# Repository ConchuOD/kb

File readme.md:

# Custom keyboard

Things that are sub-optimal:
- mounting holes are M2 when M3 would be better.
- SOD323 are needlessly small, requiring better soldering gear than is reasonable.

Thanks to Jorge Reyes for his simple T3.2 model: https://grabcad.com/library/teensy-3-1-3-2-1
Thanks also to Constantin for his eagle teensy models that I converted to use in kicad https://forum.pjrc.com/threads/24637-Updated-Teensy-3-1-and-Teensy-3-0-Eagle-libraries

After 2 years, I finally got myself a 3d printer. I might finally finish this :)

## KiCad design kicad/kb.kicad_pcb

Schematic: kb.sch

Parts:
A1: CHERRY-MX; SW_Cherry_MX_1.00u_PCB
B1: CHERRY-MX; SW_Cherry_MX_1.00u_PCB
BCKT1: CHERRY-MX; SW_Cherry_MX_1.00u_PCB
BKSP1: CHERRY-MX; SW_Cherry_MX_2.00u_PCB
BSLH1: CHERRY-MX; SW_Cherry_MX_1.00u_PCB
C1: CHERRY-MX; SW_Cherry_MX_1.00u_PCB
CAPS1: CHERRY-MX; SW_Cherry_MX_1.75u_PCB
COLON1: CHERRY-MX; SW_Cherry_MX_1.00u_PCB
COMMA1: CHERRY-MX; SW_Cherry_MX_1.00u_PCB
D1, D2, D3, D4, D5, D6, D7, D8, D9, D10, D11, D12, D13, D14, D15, D16, D17, D18, D19, D20, D21, D22, D23, D24, D25, D26, D27, D28, D29, D30, D31, D32, D33, D34, D35, D36, D37, D38, D39, D40, D41, D42, D43, D44, D45, D46, D47, D48, D49, D50, D51, D52, D53, D54, D55, D56, D57, D58, D59, D60, D61, D62, D63, D64, D65, D66, D67, D68, D69, D70, D71, D72, D73, D74, D75, D76, D77, D78, D79, D80, D81, D82, D84, D85, D86, D87, D88, D89, D90, D91, D92, D93, D94: 1N4148WS; DIODES_SOD-323
D83: CHERRY-MX; SW_Cherry_MX_1.00u_PCB
E1: CHERRY-MX; SW_Cherry_MX_1.00u_PCB
EIGHT1: CHERRY-MX; SW_Cherry_MX_1.00u_PCB
ENTER1: CHERRY-MX; SW_Cherry_MX_ISOEnter_PCB
EQL1: CHERRY-MX; SW_Cherry_MX_1.00u_PCB
ESC1: CHERRY-MX; SW_Cherry_MX_1.00u_PCB
F1, F2, F3, F4, F5, F6, F7, F8, F9, F10, F11, F12, F13: CHERRY-MX; SW_Cherry_MX_1.00u_PCB
FIVE1: CHERRY-MX; SW_Cherry_MX_1.00u_PCB
FN1: CHERRY-MX; SW_Cherry_MX_1.25u_PCB
FOUR1: CHERRY-MX; SW_Cherry_MX_1.00u_PCB
FSH1: CHERRY-MX; SW_Cherry_MX_1.00u_PCB
FSTOP1: CHERRY-MX; SW_Cherry_MX_1.00u_PCB
G1: CHERRY-MX; SW_Cherry_MX_1.00u_PCB
H1: CHERRY-MX; SW_Cherry_MX_1.00u_PCB
HASH1: CHERRY-MX; SW_Cherry_MX_1.00u_PCB
I1: CHERRY-MX; SW_Cherry_MX_1.00u_PCB
J1: CHERRY-MX; SW_Cherry_MX_1.00u_PCB
K1: CHERRY-MX; SW_Cherry_MX_1.00u_PCB
L1: CHERRY-MX; SW_Cherry_MX_1.00u_PCB
LALT1: CHERRY-MX; SW_Cherry_MX_1.25u_PCB
LCTRL1: CHERRY-MX; SW_Cherry_MX_1.25u_PCB
LOS1: CHERRY-MX; SW_Cherry_MX_1.25u_PCB
LSB1: CHERRY-MX; SW_Cherry_MX_1.00u_PCB
LSHFT1: CHERRY-MX; SW_Cherry_MX_1.25u_PCB
M1: CHERRY-MX; SW_Cherry_MX_1.00u_PCB
MINUS1: CHERRY-MX; SW_Cherry_MX_1.00u_PCB
N1, N2, N3, N4, N5, N6, N7, N8, N9, N10: CHERRY-MX; SW_Cherry_MX_1.00u_PCB
NDOT1: CHERRY-MX; SW_Cherry_MX_1.00u_PCB
NINE1: CHERRY-MX; SW_Cherry_MX_1.00u_PCB
NINUS1: CHERRY-MX; SW_Cherry_MX_1.00u_PCB
NNTER1: CHERRY-MX; SW_Cherry_MX_2.00u_Vertical_PCB
NPLUS1: CHERRY-MX; SW_Cherry_MX_2.00u_Vertical_PCB
NSLSH1: CHERRY-MX; SW_Cherry_MX_1.00u_PCB
NSTAR1: CHERRY-MX; SW_Cherry_MX_1.00u_PCB
NUMLK1: CHERRY-MX; SW_Cherry_MX_1.00u_PCB
NZERO1: CHERRY-MX; SW_Cherry_MX_1.00u_PCB
NZZERO1: CHERRY-MX; SW_Cherry_MX_1.00u_PCB
O1: CHERRY-MX; SW_Cherry_MX_1.00u_PCB
ONE1: CHERRY-MX; SW_Cherry_MX_1.00u_PCB
P1: CHERRY-MX; SW_Cherry_MX_1.00u_PCB
Q1: CHERRY-MX; SW_Cherry_MX_1.00u_PCB
R1: CHERRY-MX; SW_Cherry_MX_1.00u_PCB
RALT1: CHERRY-MX; SW_Cherry_MX_1.25u_PCB
RCTRL1: CHERRY-MX; SW_Cherry_MX_1.25u_PCB
ROS1: CHERRY-MX; SW_Cherry_MX_1.25u_PCB
RSB1: CHERRY-MX; SW_Cherry_MX_1.00u_PCB
RSHFT1: CHERRY-MX; SW_Cherry_MX_2.75u_PCB
S1: CHERRY-MX; SW_Cherry_MX_1.00u_PCB
SEVEN1: CHERRY-MX; SW_Cherry_MX_1.00u_PCB
SIX1: CHERRY-MX; SW_Cherry_MX_1.00u_PCB
SPACE1: CHERRY-MX; SW_Cherry_MX_6.25u_PCB
T1: CHERRY-MX; SW_Cherry_MX_1.00u_PCB
T32: TEENSY_3.1-3.2_DIL; TEENSY_3.0-3.2&LC_DIL
TAB1: CHERRY-MX; SW_Cherry_MX_1.50u_PCB
THREE1: CHERRY-MX; SW_Cherry_MX_1.00u_PCB
TICK1: CHERRY-MX; SW_Cherry_MX_1.00u_PCB
TP13: TestPoint; TestPoint_Pad_D1.0mm
TPCOL0, TPCOL1, TPCOL2, TPCOL3, TPCOL4, TPCOL5, TPCOL6, TPCOL7, TPCOL8, TPCOL9, TPCOL10, TPCOL11, TPCOL12: TestPoint; TestPoint_Pad_D1.0mm
TPROW0, TPROW1, TPROW2, TPROW3, TPROW4, TPROW5, TPROW6: TestPoint; TestPoint_Pad_D1.0mm
TWO1: CHERRY-MX; SW_Cherry_MX_1.00u_PCB
U1: CHERRY-MX; SW_Cherry_MX_1.00u_PCB
V1: CHERRY-MX; SW_Cherry_MX_1.00u_PCB
W1: CHERRY-MX; SW_Cherry_MX_1.00u_PCB
X1: CHERRY-MX; SW_Cherry_MX_1.00u_PCB
Y1: CHERRY-MX; SW_Cherry_MX_1.00u_PCB
Z1: CHERRY-MX; SW_Cherry_MX_1.00u_PCB
ZERO1: CHERRY-MX; SW_Cherry_MX_1.00u_PCB

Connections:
+3V3: T32.3.3V
+5V: T32.VIN
/COL0: D1.C, D2.C, D3.C, D4.C, D5.C, D6.C, D8.C, T32.0, TPCOL0.1
/COL1: D7.C, D9.C, D10.C, D11.C, D12.C, D13.C, D14.C, T32.1, TPCOL1.1
/COL2: D15.C, D16.C, D17.C, D18.C, D19.C, D20.C, D22.C, T32.2, TPCOL2.1
/COL3: D21.C, D24.C, D25.C, D26.C, D27.C, D28.C, D62.C, T32.3, TPCOL3.1
/COL4: D29.C, D30.C, D31.C, D32.C, D33.C, D34.C, D61.C, T32.4, TPCOL4.1
/COL5: D23.C, D35.C, D60.C, D64.C, D65.C, D66.C, D67.C, T32.5, TPCOL5.1
/COL6: D36.C, D37.C, D38.C, D39.C, D40.C, D63.C, T32.6, TPCOL6.1
/COL7: D42.C, D43.C, D44.C, D45.C, D46.C, T32.7, TPCOL7.1
/COL8: D48.C, D49.C, D50.C, D51.C, D52.C, D53.C, T32.8, TPCOL8.1
/COL9: D54.C, D55.C, D56.C, D57.C, D58.C, D59.C, D74.C, T32.9, TPCOL9.1
/COL10: D69.C, D70.C, D71.C, D72.C, D77.C, D79.C, D80.C, T32.10, TPCOL10.1
/COL11: D41.C, D47.C, D75.C, D76.C, D84.C, D85.C, D86.C, T32.11, TPCOL11.1
/COL12: D87.C, D88.C, D89.C, D90.C, D91.C, D92.C, T32.12, TPCOL12.1
/COL13: D68.C, D73.C, D78.C, D81.C, D82.C, D93.C, D94.C, T32.13, TP13.1
/N$1: D1.A, ESC1.SW2 (PIN-2)
/N$2: BCKT1.SW2 (PIN-2), D2.A
/N$3: D3.A, TAB1.SW2 (PIN-2)
/N$4: CAPS1.SW2 (PIN-2), D4.A
/N$5: D5.A, LSHFT1.SW2 (PIN-2)
/N$6: D6.A, LCTRL1.SW2 (PIN-2)
/N$7: D8.A, ONE1.SW2 (PIN-2)
/N$8: D9.A, Q1.SW2 (PIN-2)
/N$9: A1.SW2 (PIN-2), D10.A
/N$10: BSLH1.SW2 (PIN-2), D11.A
/N$11: D12.A, LOS1.SW2 (PIN-2)
/N$12: D13.A, TWO1.SW2 (PIN-2)
/N$13: D14.A, W1.SW2 (PIN-2)
/N$14: D15.A, S1.SW2 (PIN-2)
/N$15: D16.A, Z1.SW2 (PIN-2)
/N$16: D17.A, LALT1.SW2 (PIN-2)
/N$17: D7.A, F1.SW2 (PIN-2)
/N$18: D19.A, THREE1.SW2 (PIN-2)
/N$19: D20.A, E1.SW2 (PIN-2)
/N$20: D21.A, D83.SW2 (PIN-2)
/N$21: D22.A, X1.SW2 (PIN-2)
/N$22: D29.A, SIX1.SW2 (PIN-2)
/N$23: D18.A, F2.SW2 (PIN-2)
/N$24: D25.A, FOUR1.SW2 (PIN-2)
/N$25: D26.A, R1.SW2 (PIN-2)
/N$26: D27.A, F13.SW2 (PIN-2)
/N$27: C1.SW2 (PIN-2), D28.A
/N$28: D35.A, Y1.SW2 (PIN-2)
/N$29: D24.A, F3.SW2 (PIN-2)
/N$30: D31.A, FIVE1.SW2 (PIN-2)
/N$31: D32.A, T1.SW2 (PIN-2)
/N$32: D33.A, G1.SW2 (PIN-2)
/N$33: D34.A, V1.SW2 (PIN-2)
/N$34: D60.A, H1.SW2 (PIN-2)
/N$35: D30.A, F4.SW2 (PIN-2)
/N$36: D37.A, EIGHT1.SW2 (PIN-2)
/N$37: D38.A, I1.SW2 (PIN-2)
/N$38: D39.A, K1.SW2 (PIN-2)
/N$39: D40.A, M1.SW2 (PIN-2)
/N$40: D41.A, NUMLK1.SW2 (PIN-2)
/N$41: D36.A, F7.SW2 (PIN-2)
/N$42: D43.A, NINE1.SW2 (PIN-2)
/N$43: D44.A, O1.SW2 (PIN-2)
/N$44: D45.A, L1.SW2 (PIN-2)
/N$45: COMMA1.SW2 (PIN-2), D46.A
/N$46: D47.A, NZERO1.SW2 (PIN-2)
/N$47: D42.A, F8.SW2 (PIN-2)
/N$48: D49.A, ZERO1.SW2 (PIN-2)
/N$49: D50.A, P1.SW2 (PIN-2)
/N$50: COLON1.SW2 (PIN-2), D51.A
/N$51: D52.A, FSTOP1.SW2 (PIN-2)
/N$52: D53.A, RALT1.SW2 (PIN-2)
/N$53: D48.A, F9.SW2 (PIN-2)
/N$54: D55.A, MINUS1.SW2 (PIN-2)
/N$55: D56.A, LSB1.SW2 (PIN-2)
/N$56: D57.A, TICK1.SW2 (PIN-2)
/N$57: D58.A, FSH1.SW2 (PIN-2)
/N$58: D59.A, ROS1.SW2 (PIN-2)
/N$59: D54.A, F10.SW2 (PIN-2)
/N$60: B1.SW2 (PIN-2), D61.A
/N$61: D62.A, SPACE1.SW2 (PIN-2)
/N$62: D23.A, F5.SW2 (PIN-2)
/N$63: D64.A, SEVEN1.SW2 (PIN-2)
/N$64: D65.A, U1.SW2 (PIN-2)
/N$65: D66.A, J1.SW2 (PIN-2)
/N$66: D67.A, N10.SW2 (PIN-2)
/N$67: D68.A, NDOT1.SW2 (PIN-2)
/N$68: D63.A, F6.SW2 (PIN-2)
/N$69: D70.A, EQL1.SW2 (PIN-2)
/N$70: D71.A, RSB1.SW2 (PIN-2)
/N$71: D72.A, HASH1.SW2 (PIN-2)
/N$72: D78.A, NPLUS1.SW2 (PIN-2)
/N$73: D74.A, FN1.SW2 (PIN-2)
/N$74: D69.A, F11.SW2 (PIN-2)
/N$75: BKSP1.SW2 (PIN-2), D76.A
/N$76: D77.A, ENTER1.SW2 (PIN-2)
/N$77: D81.A, N9.SW2 (PIN-2)
/N$78: D79.A, RSHFT1.SW2 (PIN-2)
/N$79: D80.A, RCTRL1.SW2 (PIN-2)
/N$80: D75.A, F12.SW2 (PIN-2)
/N$81: D82.A, N6.SW2 (PIN-2)
/N$83: D84.A, N7.SW2 (PIN-2)
/N$84: D85.A, N4.SW2 (PIN-2)
/N$85: D86.A, N1.SW2 (PIN-2)
/N$86: D93.A, N3.SW2 (PIN-2)
/N$87: D88.A, NSLSH1.SW2 (PIN-2)
/N$88: D89.A, N8.SW2 (PIN-2)
/N$89: D90.A, N5.SW2 (PIN-2)
/N$90: D91.A, N2.SW2 (PIN-2)
/N$91: D92.A, NZZERO1.SW2 (PIN-2)
/N$92: D87.A, NSTAR1.SW2 (PIN-2)
/N$93: D94.A, NNTER1.SW2 (PIN-2)
/N$94: D73.A, NINUS1.SW2 (PIN-2)
/ROW0: ESC1.SW1 (PIN-1), F1.SW1 (PIN-1), F2.SW1 (PIN-1), F3.SW1 (PIN-1), F4.SW1 (PIN-1), F5.SW1 (PIN-1), F6.SW1 (PIN-1), F8.SW1 (PIN-1), F9.SW1 (PIN-1), F10.SW1 (PIN-1), F11.SW1 (PIN-1), F12.SW1 (PIN-1), NINUS1.SW1 (PIN-1), NSTAR1.SW1 (PIN-1), T32.17/A3, TPROW0.1
/ROW1: BKSP1.SW1 (PIN-1), EQL1.SW1 (PIN-1), F7.SW1 (PIN-1), FIVE1.SW1 (PIN-1), FOUR1.SW1 (PIN-1), MINUS1.SW1 (PIN-1), NINE1.SW1 (PIN-1), NPLUS1.SW1 (PIN-1), NSLSH1.SW1 (PIN-1), ONE1.SW1 (PIN-1), SEVEN1.SW1 (PIN-1), T32.18/A4, THREE1.SW1 (PIN-1), TPROW1.1, TWO1.SW1 (PIN-1), ZERO1.SW1 (PIN-1)
/ROW2: BCKT1.SW1 (PIN-1), E1.SW1 (PIN-1), EIGHT1.SW1 (PIN-1), LSB1.SW1 (PIN-1), N8.SW1 (PIN-1), N9.SW1 (PIN-1), NUMLK1.SW1 (PIN-1), O1.SW1 (PIN-1), P1.SW1 (PIN-1), R1.SW1 (PIN-1), RSB1.SW1 (PIN-1), SIX1.SW1 (PIN-1), T32.19/A5, TPROW2.1, W1.SW1 (PIN-1), Y1.SW1 (PIN-1)
/ROW3: COLON1.SW1 (PIN-1), D83.SW1 (PIN-1), ENTER1.SW1 (PIN-1), I1.SW1 (PIN-1), L1.SW1 (PIN-1), N5.SW1 (PIN-1), N6.SW1 (PIN-1), N7.SW1 (PIN-1), Q1.SW1 (PIN-1), S1.SW1 (PIN-1), T1.SW1 (PIN-1), T32.20/A6, TAB1.SW1 (PIN-1), TICK1.SW1 (PIN-1), TPROW3.1, U1.SW1 (PIN-1)
/ROW4: A1.SW1 (PIN-1), CAPS1.SW1 (PIN-1), COMMA1.SW1 (PIN-1), F13.SW1 (PIN-1), FSH1.SW1 (PIN-1), FSTOP1.SW1 (PIN-1), G1.SW1 (PIN-1), H1.SW1 (PIN-1), HASH1.SW1 (PIN-1), K1.SW1 (PIN-1), N2.SW1 (PIN-1), N3.SW1 (PIN-1), N4.SW1 (PIN-1), T32.21/A7, TPROW4.1, Z1.SW1 (PIN-1)
/ROW5: BSLH1.SW1 (PIN-1), C1.SW1 (PIN-1), J1.SW1 (PIN-1), LSHFT1.SW1 (PIN-1), M1.SW1 (PIN-1), N1.SW1 (PIN-1), NNTER1.SW1 (PIN-1), NZZERO1.SW1 (PIN-1), RALT1.SW1 (PIN-1), ROS1.SW1 (PIN-1), RSHFT1.SW1 (PIN-1), T32.22/A8, TPROW5.1, V1.SW1 (PIN-1), X1.SW1 (PIN-1)
/ROW6: B1.SW1 (PIN-1), FN1.SW1 (PIN-1), LALT1.SW1 (PIN-1), LCTRL1.SW1 (PIN-1), LOS1.SW1 (PIN-1), N10.SW1 (PIN-1), NDOT1.SW1 (PIN-1), NZERO1.SW1 (PIN-1), RCTRL1.SW1 (PIN-1), SPACE1.SW1 (PIN-1), T32.23/A9, TPROW6.1
GND: T32.AGND, T32.GND

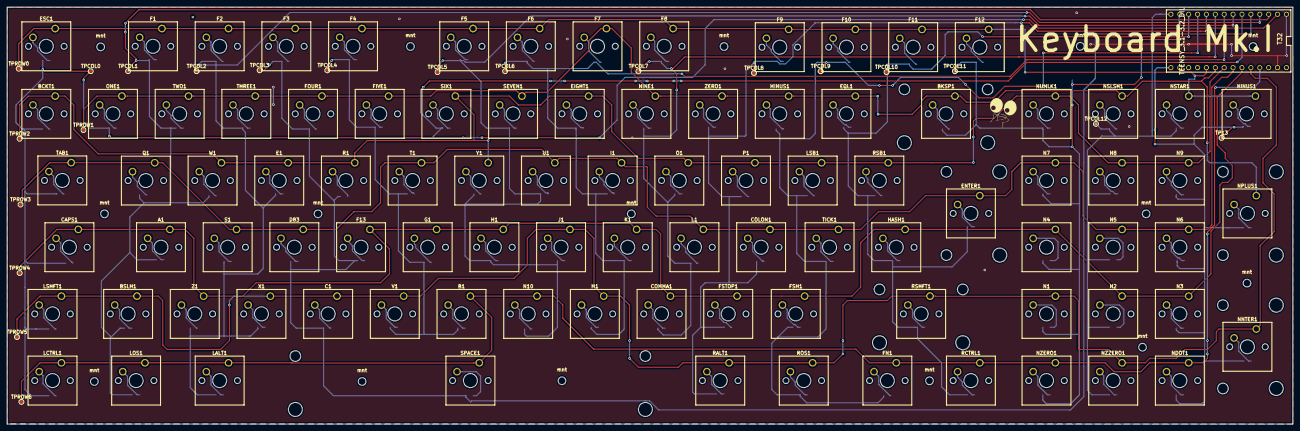
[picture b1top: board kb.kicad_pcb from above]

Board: 2 copper layers, 367.3 x 119.1 mm, 223 parts (0 on the bottom side), 115 nets.

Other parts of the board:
mnt: MountingHole_2.2mm_M2
mnt#2, mnt#3, mnt#4, mnt#5, mnt#6, mnt#7, mnt#8, mnt#9, mnt#10, mnt#11, mnt#12, mnt#13, mnt#14, mnt#15: MountingHole_2.2mm_M2

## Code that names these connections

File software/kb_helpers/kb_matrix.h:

#ifndef KB_MATRIX_H_
#define KB_MATRIX_H_

#include <kinetis.h>
#include <Arduino.h>
#include "keycodes.h"

#define COL0_PIN  0
#define COL1_PIN  1
#define COL2_PIN  2
#define COL3_PIN  3
#define COL4_PIN  4
#define COL5_PIN  5
#define COL6_PIN  6
#define COL7_PIN  7
#define COL8_PIN  8
#define COL9_PIN  9
#define COL10_PIN 10
#define COL11_PIN 11
#define COL12_PIN 12
#define COL13_PIN 13

#define ROW0_PIN  17
#define ROW1_PIN  18
#define ROW2_PIN  19
#define ROW3_PIN  20
#define ROW4_PIN  21
#define ROW5_PIN  22
#define ROW6_PIN  23

#define NUM_ROWS  7
#define NUM_COLS  14

static const uint16_t matrix_to_keycode[NUM_ROWS * NUM_COLS] = {
    KC_ESC,   KC_ONE,   KC_BTK,   KC_TAB,    KC_CAPS,  KC_LSHFT, KC_LCTRL,
    KC_F1,    KC_TWO,   KC_W,     KC_Q,      KC_A,     KC_BSLH,  KC_LOS,
    KC_F2,    KC_THREE, KC_E,     KC_S,      KC_Z,     KC_X,     KC_LALT,
    KC_F3,    KC_FOUR,  KC_R,     KC_D,      KC_F,     KC_C,     KC_SPACE,
    KC_F4,    KC_FIVE,  KC_SIX,   KC_T,      KC_G,     KC_V,     KC_B,
    KC_F5,    KC_SEVEN, KC_Y,     KC_U,      KC_H,     KC_J,     KC_N,
    KC_F6,    KC_F7,    KC_EIGHT, KC_I,      KC_K,     KC_M,     0,
    KC_F8,    KC_NINE,  KC_O,     KC_L,      KC_COMMA, 0,        0,
    KC_F9,    KC_ZERO,  KC_P,     KC_SCOLON, KC_DOT,   KC_RALT,  0,
    KC_F10,   KC_MINUS, KC_LSB,   KC_TICK,   KC_FSLSH, KC_ROS,   KC_RCTRL,
    KC_F11,   KC_EQUAL, KC_RSB,   KC_ENTER,  KC_HASH,  KC_RSHFT, KC_RCTRL,
    KC_F12,   KC_BKSP,  KC_NUMLK, KC_N7,     KC_N4,    KC_N1,    KC_N0,
    KC_NSTAR, KC_NSLSH, KC_N8,    KC_N5,     KC_N2,    KC_N0,    0,
    KC_NINUS, KC_NPLUS, KC_N9,    KC_N6,     KC_N3,    KC_NNTER, KC_NDOT
};

void setup_teensy_ports(void);

#endif /* KB_MATRIX_H_ */

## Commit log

2019-11-25 initial commit for custom kb
2019-11-25 readme
2019-11-25 more routing
2019-11-28 routing done
2019-11-30 deleting unneeded files
2019-11-30 readme update for lib attribution
2019-12-01 ready for manuf.
2019-12-10 moving labels on T32
2019-12-11 updated ignores
2019-12-11 updating files based on new ignore
2019-12-11 kicad/ -> hardware/
2019-12-11 adding teensy cores submodule
2019-12-11 initial commit on software side of things. Spent today setting up vscode and creating some (unlikely to compile) test code.
2019-12-11 attempting to make cores submodule track master directly
2019-12-13 builds at least
2019-12-13 makefile: -std=c11
2019-12-13 makefile: make clean updated to remove every leftover object
2019-12-15 validity of keyboard matrix confirmed
2019-12-16 working on matrix to LUT
2019-12-16 spitting letters into serial console
2019-12-17 preprocessor LUT for keycodes
2019-12-17 Disabling usb serial
2019-12-17 properly deleting objects etc
2019-12-17 pending exposal of keycode related functions to avoid pjrc supplied unicode based stuff - just do my own extention of stream
2019-12-18 now spitting out keys into terminal
2019-12-20 initial modifier handling
2019-12-21 repeat rate sorted. no modifiers. 1kro :joy:
2019-12-21 send via system (wrapped in IntervalTimer)
2019-12-22 20kro
2019-12-22 modifiers (and its 6kro over usb not 20)
2020-01-05 now working on windows and dupliate polling removed
2020-01-05 update tcores and rename files to avoid conflict with tcores provided usb keyboard
2022-02-17 2 years later...
2022-05-22 Create LICENSE
